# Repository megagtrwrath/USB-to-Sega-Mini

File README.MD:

# USB to Sega Mini
A Controller adapter for the Sega Saturn, MegaDrive and Genesis!

***Built on [Sonik-br's](https://github.com/sonik-br) USB2RetroConsole firmware***
Link to the firmware ***[HERE!](https://github.com/sonik-br/usb2retroconsole-fw)***

You can get a pre-built copy of the firmware for this board [here!](https://cdn.discordapp.com/attachments/704047253282619503/1441765426223775895/usb2saturn.waveshare_rp2040_zero_mega03_20251122.uf2?ex=69244db0&is=6922fc30&hm=23a919a0cd07db872d9da08c34391ca4e7c7862f3553438b56502e849349b4bc&) (Saturn only for now) 

## About this project
This github repo includes the source KICAD files for making modifications, and has it's GERBER, BOM and CPL in the Production Files folder. You may need to make modifications to find suitable parts
I have manually excluded the DB9 connector and Saturn connector as to freely allow installation of whichever you choose.

## Features:
<ul>
	<li>Support for various wired controllers (Original Xbox, 360, One, Series, PS3, PS4, PS5, Switch and any XINPUT capable device</li>
	<li>Low latency conversion, under or around 1 frame</li>
	<li>Emulation of various controllers (3D Pad [Digital and Analog modes], Arcade Racer/Steering Wheel, Mission Stick (3 axis mode), Shuttle mouse)</li>
	<li>Plug and play! No console modification required!</li>
	<li>Optional external USB power for power hungry controllers!</li>
</ul>

## To Do:
<ul>
	<li>3d printed case</li>
	<li>Further design optimizations</li>
	<li>Better documentation</li>
</ul>

## License
Copyright © 2025 Mega

This project is licensed under the **CERN-OHL-S V2** license.

This means you can:
<ul>
	<li>Use and reproduce this adapter for any purpose</li>
	<li>Make modifications to better fit your requirements</li>
	<li>Distribute this design, or any modifications you make to this design</li>
</ul>
This also requires that you:
<ul>
	<li>Give credit to the original board design</li>
	<li>Share your modifications under the exact same CERN-OHL-S V2 license</li>
	<li>Keep all copyright and licenses intact, this includes any original markings on the PCB, Logos and Project URLs present in the files. These ***cannot be removed or altered*** </lil>
<ul>

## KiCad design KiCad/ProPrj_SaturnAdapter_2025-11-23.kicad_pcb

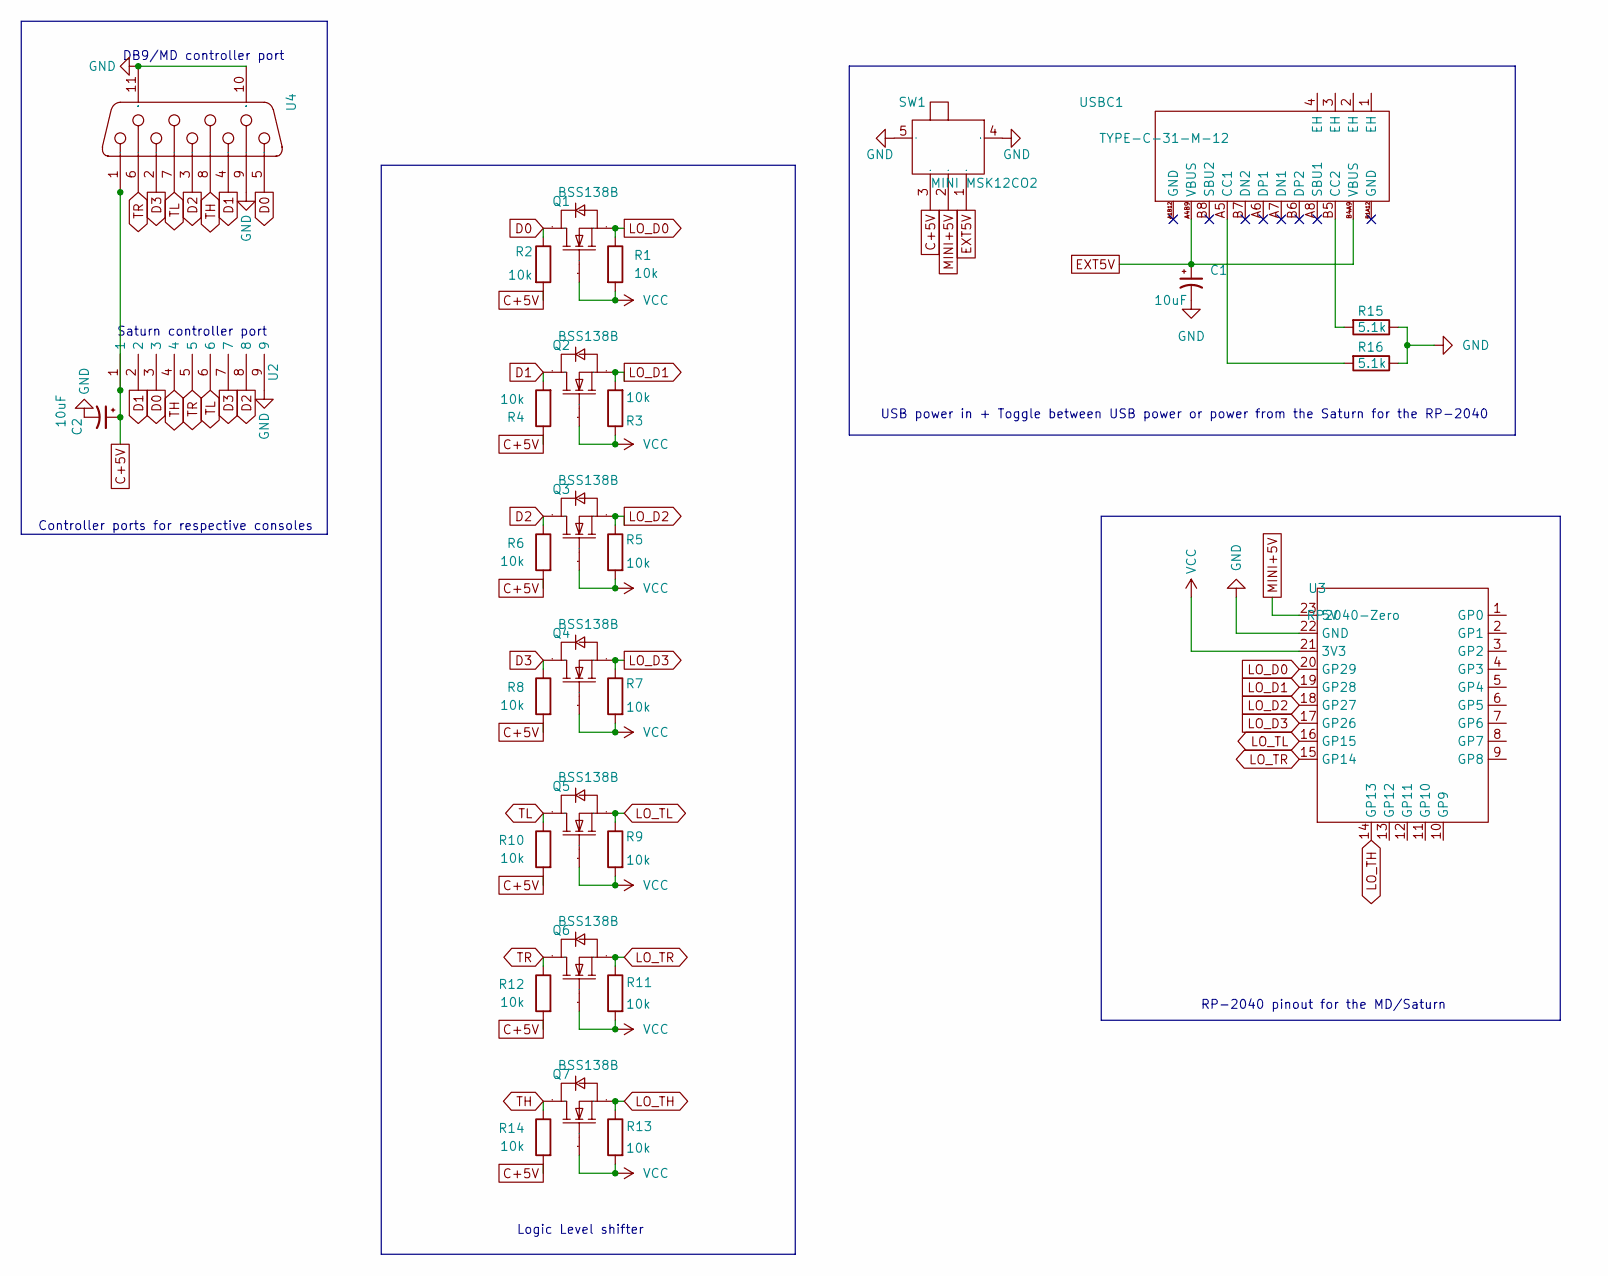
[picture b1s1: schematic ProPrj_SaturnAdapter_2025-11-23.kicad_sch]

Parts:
C1, C2: 10uF; C_1206_3216Metric_Pad1.33x1.80mm_HandSolder; MPN C13585
Q1, Q2, Q3, Q4, Q5, Q6, Q7: BSS138B; SOT-23-3_L2.9-W1.3-P1.90-LS2.4-BR; Manufacturer Part BSS138B; LCSC Part Name BSS138B
R1, R2, R3, R4, R5, R6, R7, R8, R9, R10, R11, R12, R13, R14: 10k; R0603; MPN C25804
R15, R16: 5.1k; R0603; MPN C23186
SW1: MINI MSK12CO2; SW-SMD_MSK12CO2; Manufacturer Part MINI MSK12CO2; LCSC Part Name 迷你七脚两档侧拨拨动 mini七7脚 微型拨动
U2: SATURN CONNECTOR
U3: RP2040-Zero; RP2040-ZERO DIP; Manufacturer Part RP2040-Zero; LCSC Part Name 微雪 树莓派RP2040-Zero微控制器 PICO开发板 RP2040双核处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
U4: D-SUB-DR-9PCM-CB; DB9-TH_D-SUB-DR-9PCM-CB; Manufacturer Part D-SUB-DR-9PCM-CB; LCSC Part Name 母 P数:9P
USBC1: TYPE-C-31-M-12; USB-C_SMD-TYPE-C-31-M-12_1; Manufacturer Part TYPE-C-31-M-12; LCSC Part Name Type-C 母

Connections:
C+5V: C2.1, R2.2, R4.1, R6.2, R8.2, R10.2, R12.2, R14.2, SW1.3, U2.1, U4.1; also elsewhere on the board
D0: Q1.3 (D), R2.1, U2.3, U4.5; also elsewhere on the board
D1: Q2.3 (D), R4.2, U2.2, U4.4; also elsewhere on the board
D2: Q3.3 (D), R6.1, U2.8, U4.3; also elsewhere on the board
D3: Q4.3 (D), R8.1, U2.7, U4.2; also elsewhere on the board
EXT5V: C1.1, SW1.1, USBC1.A4B9 (VBUS), USBC1.B4A9 (VBUS); also elsewhere on the board
GND: C1.2, C2.2, R15.1, R16.1, SW1.4, SW1.5, U2.9, U3.22 (GND), U4.9, U4.10 (MH1), U4.11 (MH2); also elsewhere on the board
LO_D0: Q1.2 (S), R1.1, U3.20 (GP29)
LO_D1: Q2.2 (S), R3.2, U3.19 (GP28)
LO_D2: Q3.2 (S), R5.1, U3.18 (GP27)
LO_D3: Q4.2 (S), R7.1, U3.17 (GP26)
LO_TH: Q7.2 (S), R13.1, U3.14 (GP13)
LO_TL: Q5.2 (S), R9.1, U3.16 (GP15)
LO_TR: Q6.2 (S), R11.1, U3.15 (GP14)
MINI+5V: SW1.2, U3.23 (5V)
unnamed 15: R16.2, USBC1.A5 (CC1); also elsewhere on the board
unnamed 16: R15.2, USBC1.B5 (CC2); also elsewhere on the board
TH: Q7.3 (D), R14.1, U2.4, U4.8; also elsewhere on the board
TL: Q5.3 (D), R10.1, U2.6, U4.7; also elsewhere on the board
TR: Q6.3 (D), R12.1, U2.5, U4.6; also elsewhere on the board
VCC: Q1.1 (G), Q2.1 (G), Q3.1 (G), Q4.1 (G), Q5.1 (G), Q6.1 (G), Q7.1 (G), R1.2, R3.1, R5.2, R7.2, R9.2, R11.2, R13.2, U3.21 (3V3)

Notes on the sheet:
RP-2040 pinout for the MD/Saturn
USB power in + Toggle between USB power or power from the Saturn for the RP-2040
Saturn controller port
Controller ports for respective consoles
DB9/MD controller port
Logic Level shifter

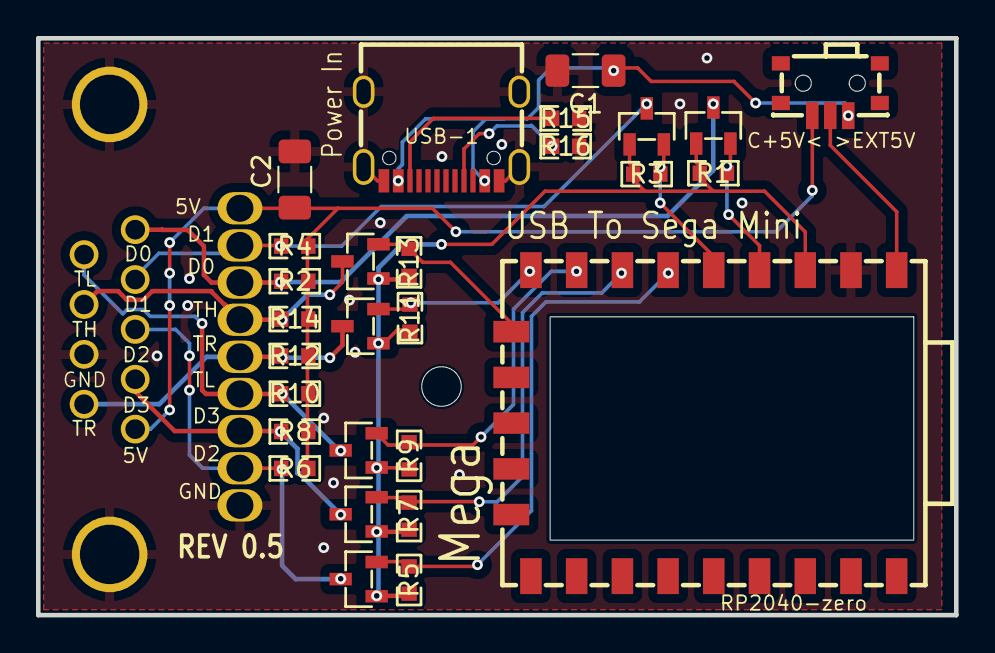
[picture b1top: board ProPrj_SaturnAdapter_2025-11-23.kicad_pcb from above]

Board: 2 copper layers, 51.0 x 32.0 mm, 30 parts (0 on the bottom side), 21 nets.

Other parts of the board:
CN1: DSUB-TH_FDB0901-M0DB300K6KF
USB-1: USB-C_SMD-TYPE-C-31-M-12_1

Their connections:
C+5V: CN1.5; also elsewhere on the board
D0: CN1.1; also elsewhere on the board
D1: CN1.2; also elsewhere on the board
D2: CN1.3; also elsewhere on the board
D3: CN1.4; also elsewhere on the board
EXT5V: USB-1.A4B9, USB-1.B4A9; also elsewhere on the board
GND: CN1.8, CN1.10, CN1.11, USB-1.1, USB-1.2, USB-1.3, USB-1.4, USB-1.A1B12, USB-1.B1A12; also elsewhere on the board
unnamed 15: USB-1.A5; also elsewhere on the board
unnamed 16: USB-1.B5; also elsewhere on the board
TH: CN1.7; also elsewhere on the board
TL: CN1.6; also elsewhere on the board
TR: CN1.9; also elsewhere on the board

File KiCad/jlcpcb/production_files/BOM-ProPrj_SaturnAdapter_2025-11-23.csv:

Comment,Designator,Footprint,LCSC,Quantity
,"Q1,Q2,Q3,Q4,Q5,Q6,Q7",SOT-23-3_L2.9-W1.3-P1.90-LS2.4-BR,C20599939,7
,SW1,SW-SMD_MSK12CO2,C2681570,1
"10kΩ","R1,R10,R11,R12,R13,R14,R2,R3,R4,R5,R6,R7,R8,R9",R0603,C3017715,14
10uF,"C1,C2",CAP-SMD_L3.2-W1.6,C122260,2
5.1kΩ,"R15,R16",R0603,C2907044,2
Val**,USB-1,USB-C_SMD-TYPE-C-31-M-12_1,C165948,1

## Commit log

2025-11-23 Initial commit - REV0.4 board
2025-11-23 Updated PCB to mark certain components as not to populated (DB9,Saturn port, RP2040-Zero)
2025-11-23 Rev 0.5 changes | Moving of USB C port next to DB-9/MD connector
2025-11-24 Update README.MD - Firmware download
2025-11-24 Revert "Updated PCB to mark certain components as not to populated (DB9,Saturn port, RP2040-Zero)"
    This reverts commit e9491987f3115d9c6acc2593fec8dd3ece14de18.
2025-11-24 Revert "Update README.MD"
    This reverts commit 4518c7a05c80f1975fa9e98247e4c894d9a959a1.
2025-11-24 Revert "Update README.MD - Firmware download"
    This reverts commit 8b334d6bd8b7a5d2e6b412f3c6f60ae97e4af0b9.
2025-11-24 Revert "Rev 0.5 changes | Moving of USB C port next to DB-9/MD connector"
    This reverts commit 421da58faffa196843ed661754ba694fad0c3bff.
2025-11-24 Update README.MD and related files | Fixed an accident where REV0.5 was pushed to Master
2025-11-24 REV0.5 INIT
2025-11-24 REV0.5 - Moved USB port next to controller port
2025-11-24 REV0.5 - Make RP2040, DB9 and Saturn socket not part of BOM and Placement files
2025-11-24 REV0.5 - Move USB and Switch around, shrink board size to more closely match REV0.4
2025-11-25 REV0.5 - Moved two of the SOT-23-3Ps to make room for a further shifting of the USB C port towards the controller plug
2025-11-25 Further adjustment of USB port placement and trace optimisation (All curved traces replaced with 45 degrees)
2025-11-25 Add mounting holes for eventual 3d printed case
2025-11-25 Add Change to central mounting hole for future case
2025-11-26 Updated schematic for neatness, and further shrank the PCB with the USB-C port brought closer to center
2025-11-27 Final alterations before prototype ordering
2025-12-09 Fix capacitors (Had it in line with the 5v rail rather than properly smoothing [facepalm ]
2025-12-28 Edits to files to facilitate prototype production, incl. gerbers.
2025-12-29 Price optimisation by changing of certain components from the Extended LCSC set to the JLCPCB Basic set + minor changes
2025-12-29 Updated Production files with prior changes
2026-01-06 Updated image for README
2026-01-06 README update
2026-02-05 README - Device emulation clarification
